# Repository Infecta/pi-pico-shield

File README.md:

## pi-pico-shield

A shield for the Raspberry Pi Pico for use as a game controller with [SpeedyPotato's Pico-Game-Controller firmware](https://github.com/speedypotato/Pico-Game-Controller)

# Disclaimer

- I am by no means someone who is knowledgeable when it comes to PCB design. This is my first ever design that has actually been produced.
- This board was meant as a drop-in replacement for the Yuancon/[Roxy](https://github.com/veroxzik/roxy-board) but due to [oversights](./repo_images/board_issue.png) the board did was not long enough to align to the screw standoffs. (EDIT: [Upon further inspection my measurements weren't off. I'm guessing the roxy was meant for the OLDER Yuan boards](./repo_images/comparison.png))

# Production

Gerbers are stored in the `_prod` folder of the repo as `gerbers.zip`

In JLCPCB you can pretty much get away with the default options offered by the site. Im not sure about other PCB manufacturing services so do your research.

# CREDITS

~~(I don't have proper time for crediting people in this README at the moment *im sorry*)~~ I have time now~

[SpeedyPotato](https://github.com/speedypotato/RP_Silicon_KiCad) | For his Pi-Pico Footprint that makes the USB test pads exposed for easy soldering

[veroxzik](https://github.com/veroxzik/roxy-board) | For their initial screwhole measurements from the roxy board

(There might be more people I forgot to credit and in that case I apologize)

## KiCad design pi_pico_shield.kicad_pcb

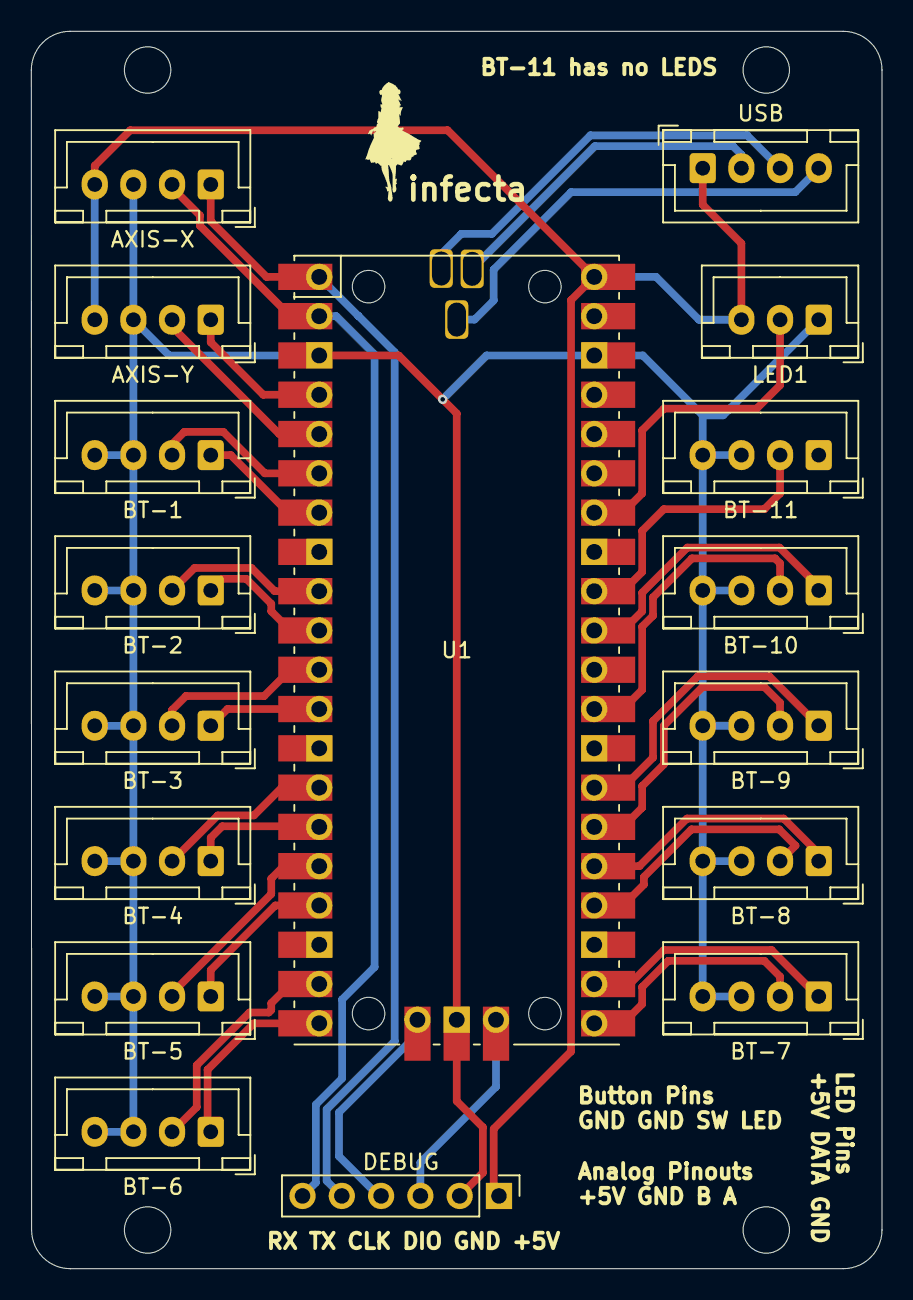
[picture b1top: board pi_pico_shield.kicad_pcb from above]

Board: 2 copper layers, 55.0 x 80.0 mm, 17 parts (0 on the bottom side), 33 nets.

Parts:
AXIS-X: Conn_01x04; JST_XH_B4B-XH-A_1x04_P2.50mm_Vertical
AXIS-Y: Conn_01x04; JST_XH_B4B-XH-A_1x04_P2.50mm_Vertical
BT-1, BT-2, BT-3, BT-4, BT-5, BT-6, BT-7, BT-8, BT-9, BT-10, BT-11: Conn_01x04; JST_XH_B4B-XH-A_1x04_P2.50mm_Vertical
DEBUG: Conn_01x06; PinHeader_1x06_P2.54mm_Vertical
LED1: Conn_01x03; JST_XH_B3B-XH-A_1x03_P2.50mm_Vertical
U1: Pico; RPi_Pico_SMD_TH
USB: Conn_01x04; JST_XH_B4B-XH-A_1x04_P2.50mm_Vertical

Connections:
+5V: AXIS-X.4, AXIS-Y.4, DEBUG.1, LED1.3, U1.40 (VBUS), USB.1
AXIS-X_A: AXIS-X.1, DEBUG.5, U1.1 (GPIO0)
AXIS-X_B: AXIS-X.2, DEBUG.6, U1.2 (GPIO1)
AXIS-Y_A: AXIS-Y.1, U1.4 (GPIO2)
AXIS-Y_B: AXIS-Y.2, U1.5 (GPIO3)
BT-1_LED: BT-1.1, U1.7 (GPIO5)
BT-1_SW: BT-1.2, U1.6 (GPIO4)
BT-2_LED: BT-2.1, U1.10 (GPIO7)
BT-2_SW: BT-2.2, U1.9 (GPIO6)
BT-3_LED: BT-3.1, U1.12 (GPIO9)
BT-3_SW: BT-3.2, U1.11 (GPIO8)
BT-4_LED: BT-4.1, U1.15 (GPIO11)
BT-4_SW: BT-4.2, U1.14 (GPIO10)
BT-5_LED: BT-5.1, U1.17 (GPIO13)
BT-5_SW: BT-5.2, U1.16 (GPIO12)
BT-6_LED: BT-6.1, U1.20 (GPIO15)
BT-6_SW: BT-6.2, U1.19 (GPIO14)
BT-7_LED: BT-7.1, U1.22 (GPIO17)
BT-7_SW: BT-7.2, U1.21 (GPIO16)
BT-8_LED: BT-8.1, U1.25 (GPIO19)
BT-8_SW: BT-8.2, U1.24 (GPIO18)
BT-9_LED: BT-9.1, U1.27 (GPIO21)
BT-9_SW: BT-9.2, U1.26 (GPIO20)
BT-10_LED: BT-10.1, U1.31 (GPIO26_ADC0)
BT-10_SW: BT-10.2, U1.29 (GPIO22)
BT-11_SW: BT-11.2, U1.32 (GPIO27_ADC1)
D+: U1.TP3, USB.3
D-: U1.TP2, USB.2
GND: AXIS-X.3, AXIS-Y.3, BT-1.3, BT-1.4, BT-2.3, BT-2.4, BT-3.3, BT-3.4, BT-4.3, BT-4.4, BT-5.3, BT-5.4, BT-6.3, BT-6.4, BT-7.3, BT-7.4, BT-8.3, BT-8.4, BT-9.3, BT-9.4, BT-10.3, BT-10.4, BT-11.3, BT-11.4, DEBUG.2, LED1.1, U1.3 (GND), U1.38 (GND), U1.42 (GND)
LED-WS2812B: LED1.2, U1.34 (GPIO28_ADC2)
SWCLK: DEBUG.4, U1.41 (SWCLK)
SWDIO: DEBUG.3, U1.43 (SWDIO)
U_GND: U1.TP1, USB.4

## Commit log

2024-08-04 Fix duplicate RX silkscreens. Clean up traces. Update Gerbers
